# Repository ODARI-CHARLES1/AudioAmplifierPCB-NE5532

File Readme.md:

**NE5532 AUDIO AMPLIFIER PROJECT**

A compact stereo audio amplifier built around the NE5532 dual low-noise op-amp, designed for clean pre-amplification of line-level audio signals.

Ideal for hobbyists, DIY audio enthusiasts, and students learning analog circuit design and PCB layout using KiCad.

---

### OVERVIEW

This project demonstrates the design of a low-noise, high-fidelity preamplifier for audio applications using the NE5532 operational amplifier.

The circuit boosts small input signals (around 0.3 V) to a level suitable for driving power amplifiers, active speakers, or audio ADCs.

Main features include:

* Input and output jacks (3.5 mm or RCA)
* ±12 V regulated power supply
* Optional volume control
* Proper decoupling for low noise

---

### FEATURES

* Adjustable gain (typically 10×)
* Low noise (< 5 nV/√Hz)
* Powered by ±12 V regulated supply
* Stereo operation (left & right channels)
* Works with standard 3.5 mm jacks
* Designed in KiCad (THT or SMD components supported)

---

### BLOCK DIAGRAM

Audio Input → Coupling Capacitor → NE5532 Amplifier → Output Capacitor → Audio Output

        ↑

      Feedback Network

        ↓

      Gain Control

---

### POWER SUPPLY

The amplifier runs on a ±12 V dual supply for low distortion and good headroom.

You can generate it using:

1. Dual-output DC-DC converter (e.g., Murata NMA1212SC, RECOM RB-1212D, MeanWell DCWN03)
2. Linear regulators (LM7812 and LM7912) with a center-tapped transformer

Add 100 nF and 10 µF decoupling capacitors close to the op-amp power pins.

---

### TYPICAL CIRCUIT COMPONENTS

| Component | Typical Value        | Description                       |
| --------- | -------------------- | --------------------------------- |
| U1        | NE5532P              | Dual op-amp IC                    |
| R1, R3    | 10 kΩ               | Input resistors                   |
| R2, R4    | 100 kΩ              | Feedback resistors (gain ≈ 10×) |
| C1, C2    | 1 µF film           | Input coupling capacitors         |
| C3, C4    | 100 µF electrolytic | Output coupling capacitors        |
| C5–C8    | 100 nF               | Power decoupling capacitors       |
| VR1       | 10 kΩ log           | Volume potentiometer (optional)   |

---

### AUDIO JACK PINOUT

| Pin | Label                       | Function     |
| --- | --------------------------- | ------------ |
| T   | Tip                         | Audio signal |
| S   | Sleeve                      | Ground       |
| G   | Switch or detect (optional) |              |

For stereo 3.5 mm jacks:

Tip = Left  Ring = Right  Sleeve = Ground

---

### DESIGN NOTES

* Use **film capacitors** in the signal path for better sound.
* Keep input and output grounds separate from power ground (star grounding).
* Place **decoupling capacitors** very close to the NE5532 pins.
* Pin-compatible upgrade options:  **OPA2134** ,  **LM4562** , etc.

---

### TOOLS USED

* KiCad 8.0+ for schematic and PCB layout
* LTSpice or Falstad for simulation
* JLCPCB / PCBWay for fabrication
* GitHub for version control and documentation

---

### POWER CONNECTIONS

| Pin    | Description     |
| ------ | --------------- |
| +12 V  | Positive supply |
| GND    | Ground          |
| −12 V | Negative supply |

For modules like RB-1212D:

VIN+ → +12 V input

VIN− → GND

VOUT+ → +12 V output

VOUT− → −12 V output

COM → GND

---

### TESTING STEPS

1. Connect ±12 V supply.
2. Apply a 0.3 V RMS sine wave to the input.
3. Measure the output with a 10 kΩ load.
4. Expect output ≈ 3 V RMS (gain ≈ 10×).
5. Check waveform for clean, undistorted signal.

---

### PCB LAYOUT TIPS

* Keep audio traces short and away from power paths.
* Use a full ground plane.
* Separate analog ground from power ground.
* Label all connectors and mounting holes clearly.

---

### REPOSITORY STRUCTURE

NE5532_Audio_Amplifier

│

├── schematic → NE5532_Preamp.kicad_sch

├── pcb → NE5532_Preamp.kicad_pcb

├── docs → README.docx, wiring_diagram.png

├── simulations → NE5532_Preamp.asc

└── LICENSE

---

### LICENSE

This project is released under the  **MIT License** .

You may use, modify, and distribute it for personal or educational projects.

---

### ACKNOWLEDGEMENTS

* NE5532 Datasheet — Texas Instruments
* KiCad Open Source Community
* DIYAudio Forum Contributors

---

### FUTURE UPGRADES

* Add tone control (bass/treble)
* Integrate headphone driver (TPA6120, LM4881)
* Convert to full SMD version
* Optional balanced XLR input stage

---

**Clean, simple, analog sound — powered by the NE5532.**

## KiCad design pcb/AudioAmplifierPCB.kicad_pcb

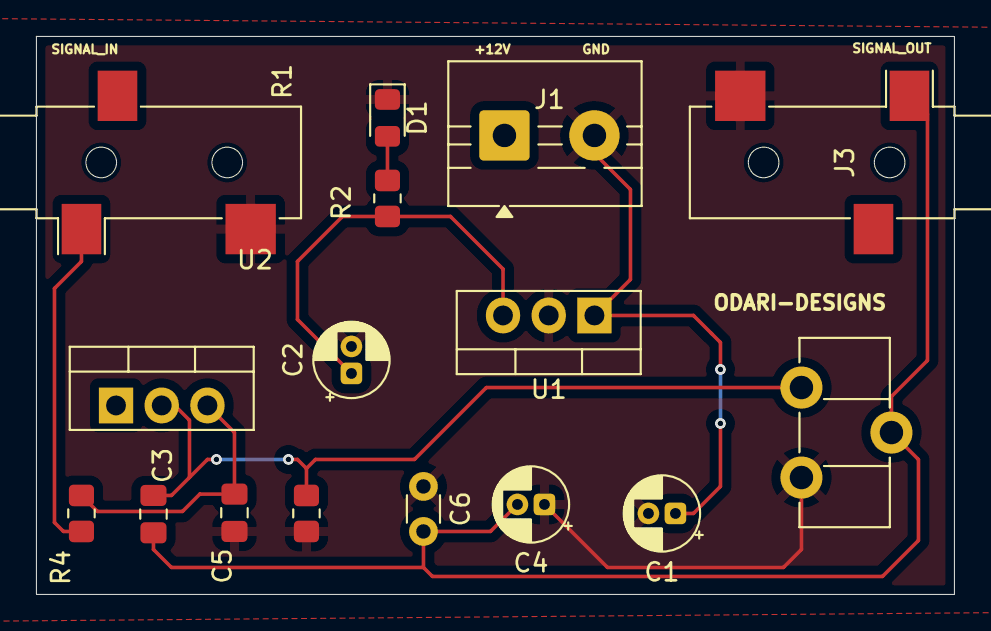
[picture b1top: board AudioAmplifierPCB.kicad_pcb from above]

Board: 2 copper layers, 51.0 x 31.0 mm, 16 parts (0 on the bottom side), 8 nets.

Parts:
C1: 0.33uF; CP_Radial_D4.0mm_P1.50mm
C2: 0.1uF; CP_Radial_D4.0mm_P1.50mm
C3: 0.47pF; C_0805_2012Metric_Pad1.18x1.45mm_HandSolder
C4: 22uF; CP_Radial_D4.0mm_P1.50mm
C5: 0.33uF; C_0805_2012Metric_Pad1.18x1.45mm_HandSolder
C6: 0.1uF; C_Disc_D3.0mm_W1.6mm_P2.50mm
D1: LED; LED_0805_2012Metric_Pad1.15x1.40mm_HandSolder
J1: Screw_Terminal_01x02; TerminalBlock_MaiXu_MX126-5.0-02P_1x02_P5.00mm
J2, J3: AudioJack2_Ground; Jack_3.5mm_CUI_SJ-3523-SMT_Horizontal
R1: 10K; R_0805_2012Metric_Pad1.20x1.40mm_HandSolder
R2: 1k; R_0805_2012Metric_Pad1.20x1.40mm_HandSolder
R4: 100K; R_0805_2012Metric_Pad1.20x1.40mm_HandSolder
RV1: 10k; Potentiometer_Piher_PT-10-H05_Horizontal
U1: LM7812_TO220; TO-220-3_Vertical
U2: NE5534; TO-220-3_Vertical

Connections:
+12V: C2.1, R2.1, U1.3 (VO)
GND: C1.2, C2.2, C4.1, C5.1, C6.1, D1.1 (K), J1.2, J2.T, J3.T, R1.2, RV1.3, U1.2 (GND)
unnamed: C3.2, C4.2, C6.2, J3.S, RV1.2
unnamed: D1.2 (A), R2.2
unnamed: C1.1, J1.1, U1.1 (VI)
unnamed: J2.S, R4.1
unnamed: C5.2, R4.2, U2.3 (+)
unnamed: C3.1, R1.1, RV1.1, U2.2 (-)

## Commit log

2025-10-19 added LED for power monitoring
2025-10-19 led for power monitoring
2025-10-20 designing pcb
2025-10-21 docs(readme) added a pcb snapshot
2025-10-21 PCB snapshot
2025-10-21 deleted backup files
